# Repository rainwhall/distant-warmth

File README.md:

# distant-warmth

> <h2> <i>“	......Somehow, it feels warm here.	”</i></h2>

</br>

<p>A simple PCB keychain of the Nightcord at 25's group symbol! In the dark (or grasped in your hand), a LED lights up and something vibrates with the push of a button.
It may not do much, but at least it'll get you through this dark night...</p>
</br>

> <p><i>""This place" is what's so warm..."</i></p>
<h3>Schematic</h3>

</br>

<h3>PCB View</h3>

</br>

<h3>3D View</h3>

</br>

> <p><i>"I'll keep enjoying this "warmth" a little longer..."</i></p>
<h3>Components used:</h3>
<ul>
  <li>1x 5.0mm LED (any colour you want!)</li>
  <li>1x 6.0mm push button</li>
  <li>1x CR2032 battery cell</li>
  <li>1x motor disc</li>
  <li>2x NPC transistor</li>
  <li>3x 4.7K resistor</li>
  <li>1x 470R resistor</li>
</ul>

</br>
<i>Made for 

[Solder](https://solder.hackclub.com/)

</i>
<i>@rainwhal on slack</i>

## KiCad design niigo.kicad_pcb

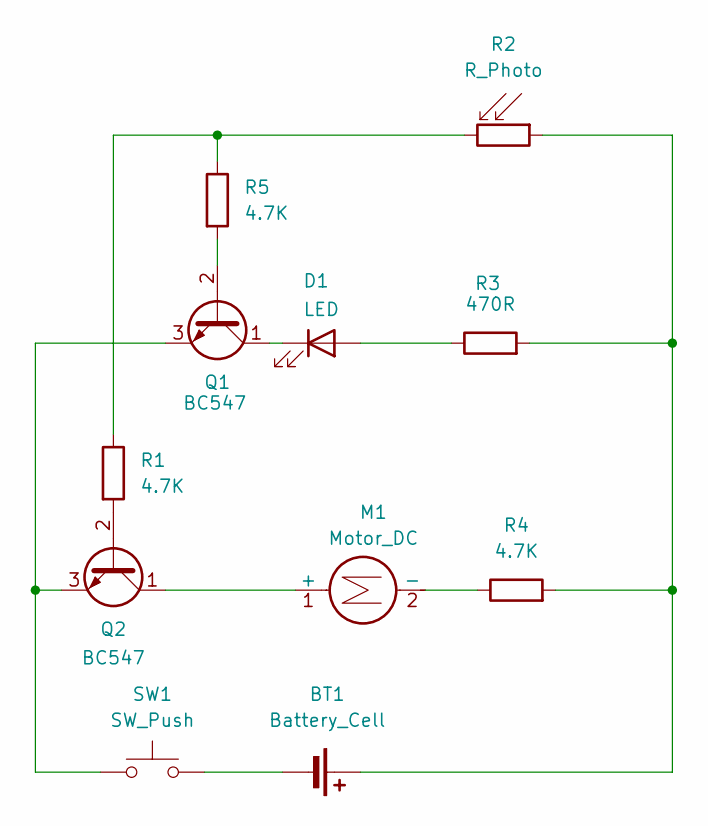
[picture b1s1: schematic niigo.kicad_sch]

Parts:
BT1: Battery_Cell; BatteryHolder_Keystone_3034_1x20mm
D1: LED; LED_D5.0mm
M1: Motor_DC; PinHeader_2x01_P1.00mm_Horizontal
Q1, Q2: BC547; TO-92_Inline
R1, R4, R5: 4.7K; R_Axial_DIN0207_L6.3mm_D2.5mm_P7.62mm_Horizontal
R2: R_Photo; R_LDR_5.1x4.3mm_P3.4mm_Vertical
R3: 470R; R_Axial_DIN0207_L6.3mm_D2.5mm_P7.62mm_Horizontal
SW1: SW_Push; SW_PUSH_6mm

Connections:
unnamed: BT1.1 (+), R2.1, R3.2, R4.2
unnamed: BT1.2 (-), SW1.2
unnamed: D1.2 (A), R3.1
unnamed: D1.1 (K), Q1.1 (C)
unnamed: M1.1 (+), Q2.1 (C)
unnamed: M1.2 (-), R4.1
unnamed: Q1.2 (B), R5.2
unnamed: Q1.3 (E), Q2.3 (E), SW1.1
unnamed: Q2.2 (B), R1.2
unnamed: R1.1, R2.2, R5.1

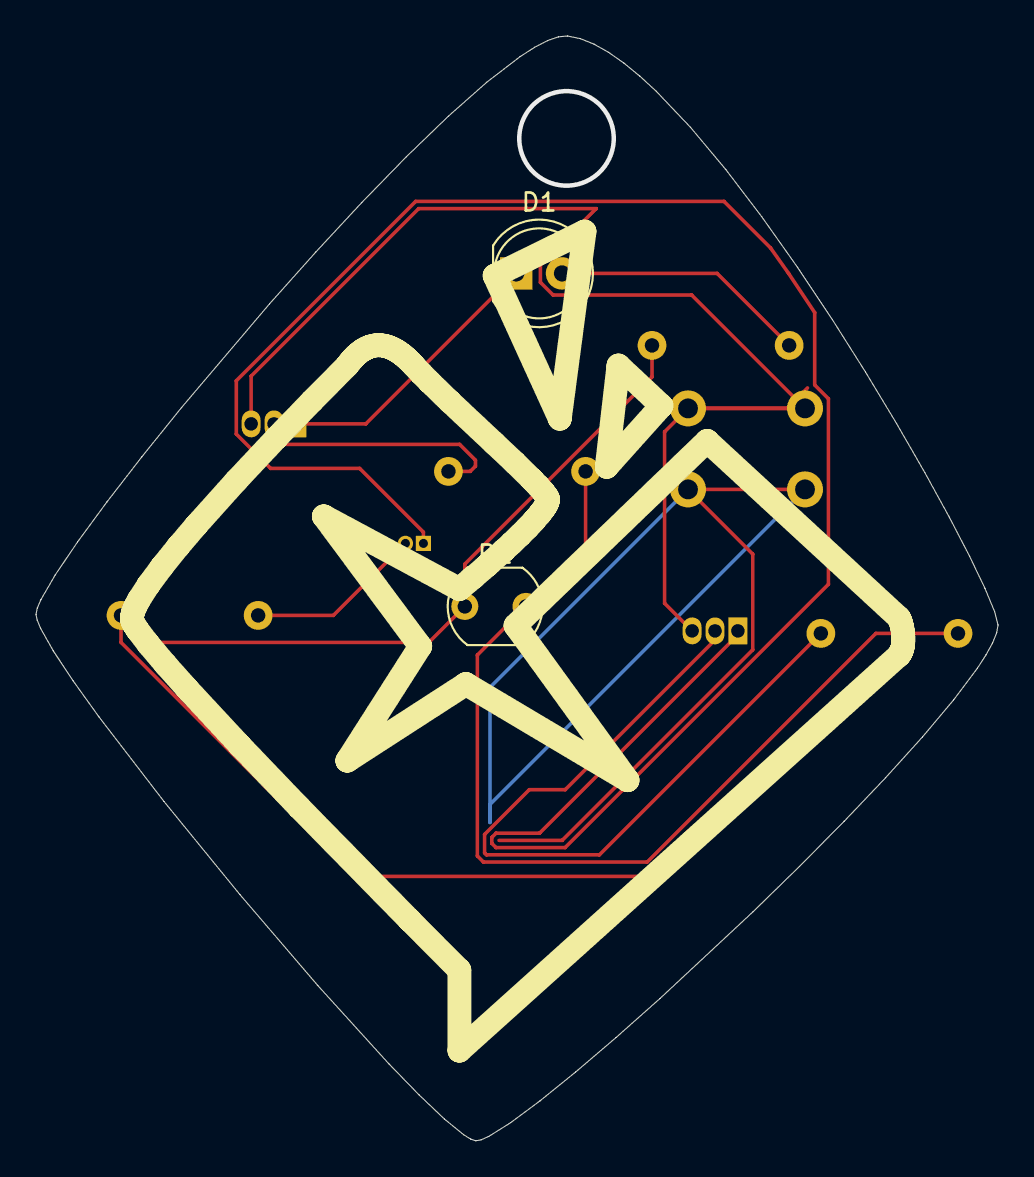
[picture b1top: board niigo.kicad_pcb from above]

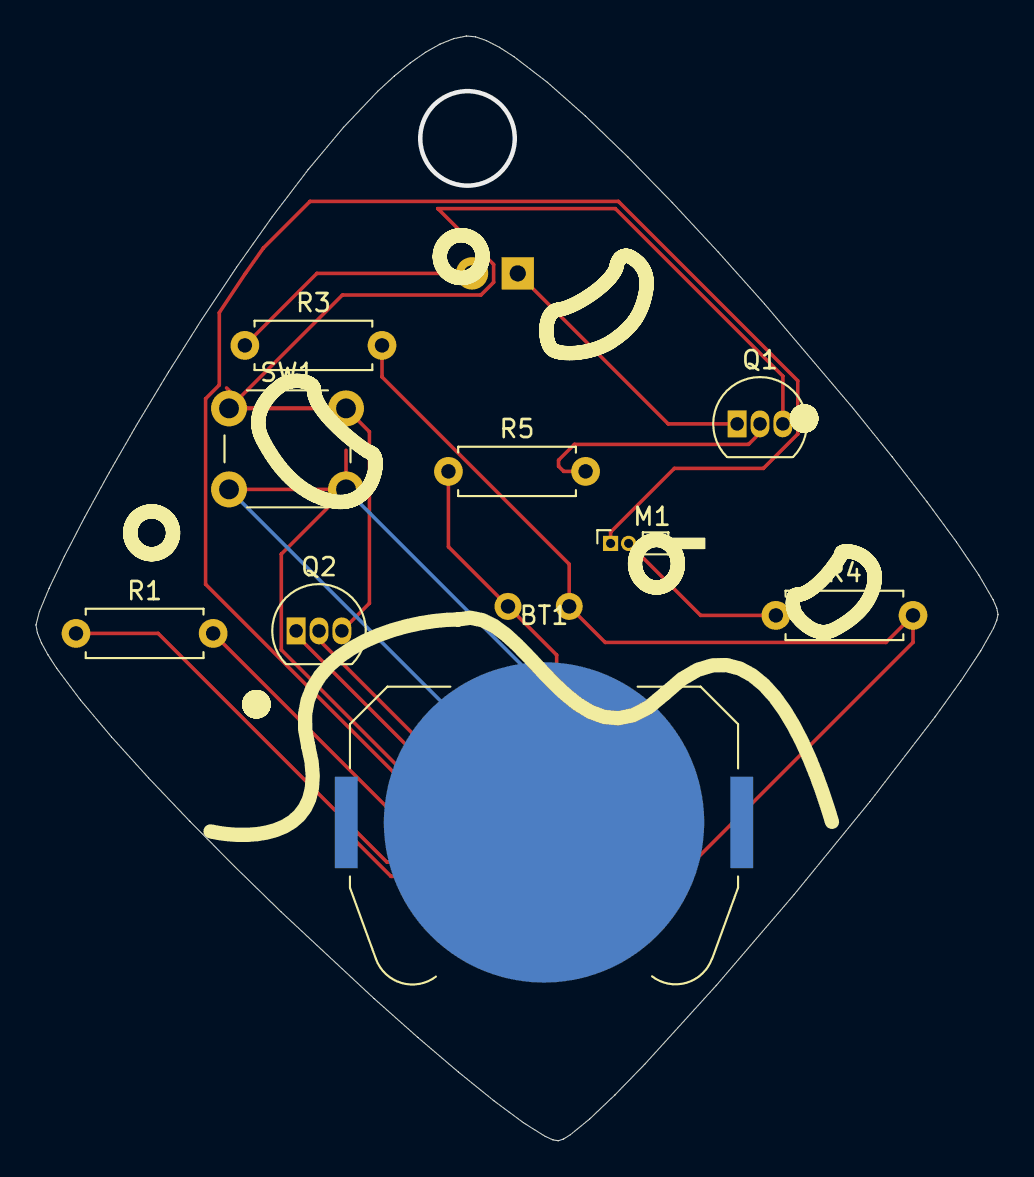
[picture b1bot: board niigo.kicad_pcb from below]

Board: 2 copper layers, 53.4 x 61.4 mm, 11 parts (9 on the bottom side), 10 nets.

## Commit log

2025-06-01 first ver! (no motor, led only)
2025-06-01 v2.0 (+ .gbr and .srl files!)
    v2.0 adds a vibrating motor with the motor disc given in the set (and more resistors...) and the gerbel and drill files needed for submission have been uploaded!
2025-06-01 Update README.md
    small things! forgot about the motor
2025-06-01 reuploaded _pcb file
    just in case.... (wasnt sure if changes saved)
